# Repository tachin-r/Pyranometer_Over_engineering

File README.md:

# Pyranometer Over-engineering ☀️⚡

Modular High-Precision Pyranometer KiCad Hardware Project.

---

## 📑 Project Structure & Interactive Online Viewers

Explore the schematics and PCB layouts interactively directly in your browser powered by **KiCanvas** (no installation required):

| Board / Module | Description | Interactive Project (Schematic + PCB) | Schematic Only | PCB Only |
| :--- | :--- | :---: | :---: | :---: |
| **L1_Analog** | Analog Front-End & Sensor Interface | [🚀 Open L1 Board](https://kicanvas.org/?github=https://github.com/tachin-r/Pyranometer_Over_engineering/tree/main/L1_Analog) | [🔍 Schematic](https://kicanvas.org/?github=https://github.com/tachin-r/Pyranometer_Over_engineering/blob/main/L1_Analog/L1_Analog.kicad_sch) | [🔍 PCB](https://kicanvas.org/?github=https://github.com/tachin-r/Pyranometer_Over_engineering/blob/main/L1_Analog/L1_Analog.kicad_pcb) |
| **L2_MCU** | Microcontroller Processing Board | [🚀 Open L2 Board](https://kicanvas.org/?github=https://github.com/tachin-r/Pyranometer_Over_engineering/tree/main/L2_MCU) | [🔍 Schematic](https://kicanvas.org/?github=https://github.com/tachin-r/Pyranometer_Over_engineering/blob/main/L2_MCU/L2_MCU.kicad_sch) | [🔍 PCB](https://kicanvas.org/?github=https://github.com/tachin-r/Pyranometer_Over_engineering/blob/main/L2_MCU/L2_MCU.kicad_pcb) |
| **L3_Switching** | Power Management & Switching Regulators | [🚀 Open L3 Board](https://kicanvas.org/?github=https://github.com/tachin-r/Pyranometer_Over_engineering/tree/main/L3_Switching) | [🔍 Schematic](https://kicanvas.org/?github=https://github.com/tachin-r/Pyranometer_Over_engineering/blob/main/L3_Switching/L3_Switching.kicad_sch) | [🔍 PCB](https://kicanvas.org/?github=https://github.com/tachin-r/Pyranometer_Over_engineering/blob/main/L3_Switching/L3_Switching.kicad_pcb) |
| **LM2596 HW-411** | Reverse-Engineered Buck Converter Module | [🚀 Open LM2596](https://kicanvas.org/?github=https://github.com/tachin-r/Pyranometer_Over_engineering/tree/main/reverse_component/LM2596_HW411) | [🔍 Schematic](https://kicanvas.org/?github=https://github.com/tachin-r/Pyranometer_Over_engineering/blob/main/reverse_component/LM2596_HW411/LM2596_HW411.kicad_sch) | [🔍 PCB](https://kicanvas.org/?github=https://github.com/tachin-r/Pyranometer_Over_engineering/blob/main/reverse_component/LM2596_HW411/LM2596_HW411.kicad_pcb) |

---

## 🛠️ Boards Overview

### 1. `L1_Analog` (Sensor Front-End)
* Precision Analog Signal Conditioning stage designed for low-noise measurement of solar irradiance sensor signals (Pyranometer Thermopile / Photodiode).

### 2. `L2_MCU` (Processing & Control)
* Primary microcontroller board responsible for high-resolution ADC sampling, calibration algorithms, digital filtering, and telemetry communication.

### 3. `L3_Switching` (Power Distribution)
* Power supply unit (PSU) providing efficient switching regulation, clean power rail generation, and noise filtering for sensitive analog circuitry.

### 4. `reverse_component/LM2596_HW411`
* Reverse-engineered KiCad schematic and PCB layout of the common LM2596 HW-411 DC-DC step-down converter module, used for reference, testing, and validation.

---

## 🚀 Working with KiCad

This project is organized as a **modular multi-board system**:
* Each sub-directory contains its own standalone KiCad project file (`.kicad_pro`).
* To view or edit a board, open the corresponding `.kicad_pro` file inside its respective directory.

---

## 🔬 Capstone Documentation & Laboratory Calibration

* **[☀️ Solar Simulator Preparation & Contact Guide](file:///c:/Users/usEr/Documents/KiCad/10.0/projects/Pyranometer_Over_engineering/Report_doc/SOLAR_SIMULATOR_GUIDE.md)**: Contact templates, technical phone checklists, and procedures for using the **Solar Light XPS-300** at ATTAC / Nano Central Lab (Building 55, 3rd Floor).
* **[📷 Perfboard Photo & Figure Insertion Guide](file:///c:/Users/usEr/Documents/KiCad/10.0/projects/Pyranometer_Over_engineering/Report_doc/PHOTO_GUIDE_PERFBOARD.md)**: Complete image checklist and tips for inserting hardware photos into the report.
* **[📄 Capstone Progress Report V2 (.docx)](file:///c:/Users/usEr/Documents/KiCad/10.0/projects/Pyranometer_Over_engineering/Report_doc/69_IoT_Project1_Report_V2.docx)**: Official 5-chapter thesis report draft formatted to KMITL guidelines.

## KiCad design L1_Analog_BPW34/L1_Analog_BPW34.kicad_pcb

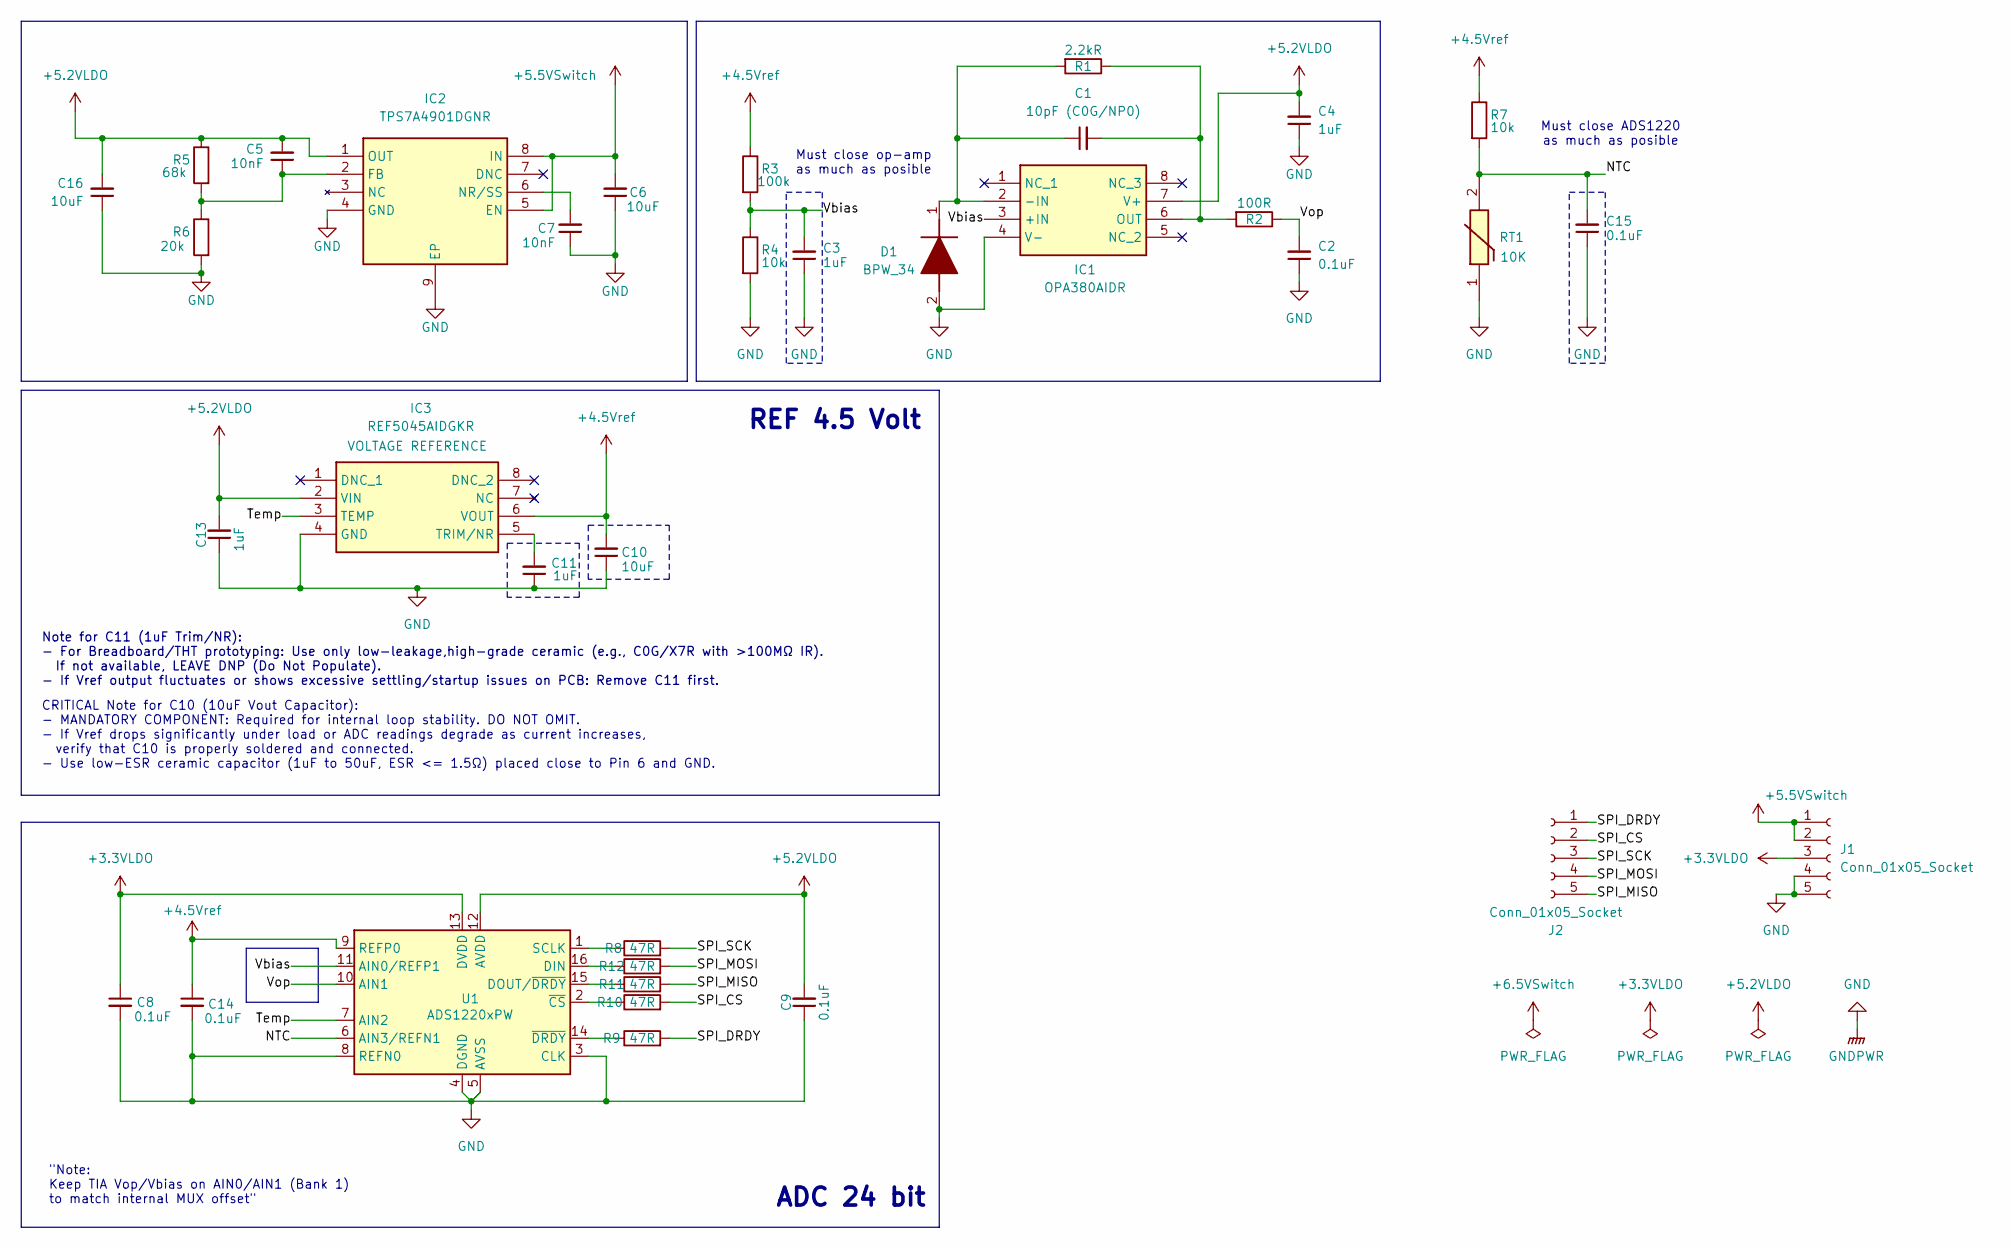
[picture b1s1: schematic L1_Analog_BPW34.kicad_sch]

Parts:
C1: 10pF (C0G/NP0); C_0805_2012Metric
C2, C8, C9, C14, C15: 0.1uF; C_0805_2012Metric
C3, C4, C11, C13: 1uF; C_0805_2012Metric
C5, C7: 10nF; C_0805_2012Metric
C6, C10, C16: 10uF; C_0805_2012Metric
D1: BPW_34; BPW34; Mouser Part Number 720-BPW34
IC1: OPA380AIDR; SOIC127P600X175-8N; Manufacturer_Part_Number OPA380AIDR; Mouser Part Number 595-OPA380AIDR
IC2: TPS7A4901DGNR; SOP65P490X110-9N; Manufacturer_Part_Number TPS7A4901DGNR; Mouser Part Number 595-TPS7A4901DGNR
IC3: REF5045AIDGKR; SOP65P490X110-8N; Mouser Part Number 595-REF5045AIDGKR
J1, J2: Conn_01x05_Socket; PinSocket_1x05_P2.54mm_Vertical
R1: 2.2kR; R_0805_2012Metric
R2: 100R; R_0805_2012Metric
R3: 100k; R_0805_2012Metric
R4, R7: 10k; R_0805_2012Metric
R5: 68k; R_0805_2012Metric
R6: 20k; R_0805_2012Metric
R8, R9, R10, R11, R12: 47R; R_0805_2012Metric
RT1: 10K; 103AT2; Manufacturer_Part_Number 103AT-2; Mouser Part Number 954-103AT-2
U1: ADS1220xPW; TSSOP-16_4.4x5mm_P0.65mm

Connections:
+3.3VLDO: C8.1, J1.3, U1.13 (DVDD)
+4.5Vref: C10.2, C14.1, IC3.6 (VOUT), R3.1, R7.1, U1.9 (REFP0)
+5.2VLDO: C4.2, C5.2, C9.2, C13.2, C16.2, IC1.7 (V+), IC2.1 (OUT), IC3.2 (VIN), R5.1, U1.12 (AVDD)
+5.5VSwitch: C6.2, IC2.5 (EN), IC2.8 (IN), J1.1, J1.2
/NTC: C15.2, R7.2, RT1.2, U1.6 (AIN3/REFN1)
/SPI_CS: J2.2, R10.2
/SPI_DRDY: J2.1, R9.2
/SPI_MISO: J2.5, R11.2
/SPI_MOSI: J2.4, R12.2
/SPI_SCK: J2.3, R8.2
/Temp: IC3.3 (TEMP), U1.7 (AIN2); also elsewhere on the board
/Vbias: C3.2, IC1.3 (+IN), R3.2, R4.1, U1.11 (AIN0/REFP1)
/Vop: C2.2, R2.1, U1.10 (AIN1)
GND: C2.1, C3.1, C4.1, C6.1, C7.1, C8.2, C9.1, C10.1, C11.1, C13.1, C14.2, C15.1, C16.1, D1.2 (A), IC1.4 (V-), IC2.4 (GND), IC2.9 (EP), IC3.4 (GND), J1.4, J1.5, R4.2, R6.2, RT1.1, U1.3 (CLK), U1.4 (DGND), U1.5 (AVSS), U1.8 (REFN0); also elsewhere on the board
unnamed: C1.1, D1.1 (K), IC1.2 (-IN), R1.2
unnamed: C1.2, IC1.6 (OUT), R1.1, R2.2
unnamed: C5.1, IC2.2 (FB), R5.2, R6.1
unnamed: C7.2, IC2.6 (NR/SS)
unnamed: C11.2, IC3.5 (TRIM/NR)
unnamed: R12.1, U1.16 (DIN)
unnamed: R11.1, U1.15 (DOUT/~DRDY)
unnamed: R8.1, U1.1 (SCLK)
unnamed: R10.1, U1.2 (~CS)
unnamed: R9.1, U1.14 (~DRDY)

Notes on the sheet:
Note for C11 (1uF Trim/NR): - For Breadboard/THT prototyping: Use only low-leakage,high-grade ceramic (e.g., C0G/X7R with >100MΩ IR). If not available, LEAVE DNP (Do Not Populate). - If Vref output fluctuates or shows excessive settling/startup issues on PCB: Remove C11 first.
"Note: Keep TIA Vop/Vbias on AIN0/AIN1 (Bank 1) to match internal MUX offset"
Must close ADS1220 as much as posible
Must close op-amp as much as posible
ADC 24 bit
CRITICAL Note for C10 (10uF Vout Capacitor): - MANDATORY COMPONENT: Required for internal loop stability. DO NOT OMIT. - If Vref drops significantly under load or ADC readings degrade as current increases, verify that C10 is properly soldered and connected. - Use low-ESR ceramic capacitor (1uF to 5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
REF 4.5 Volt

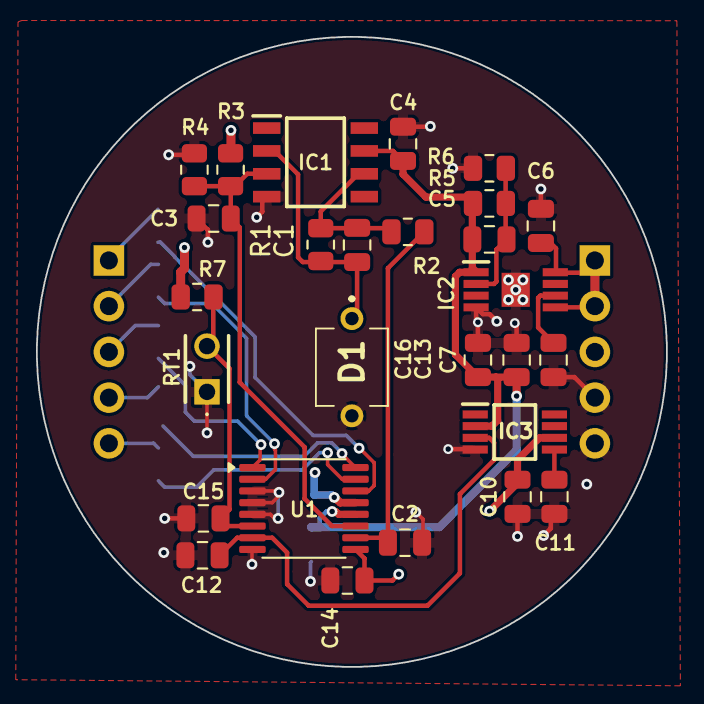
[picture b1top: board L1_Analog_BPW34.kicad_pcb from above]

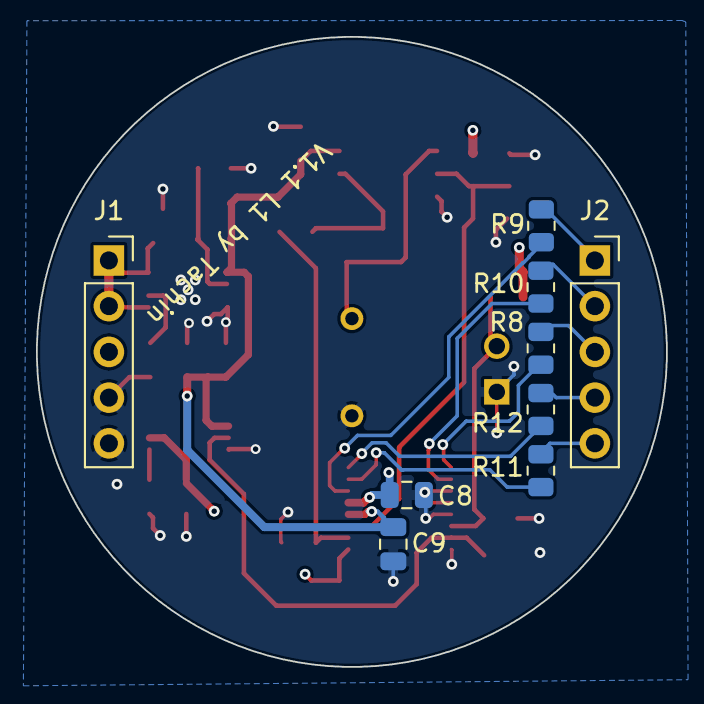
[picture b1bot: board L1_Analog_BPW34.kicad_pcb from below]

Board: 4 copper layers, 35.0 x 35.0 mm, 36 parts (9 on the bottom side), 24 nets.

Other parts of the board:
C12: 0.1uF; C_0805_2012Metric

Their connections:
/Temp: C12.2; also elsewhere on the board
GND: C12.1; also elsewhere on the board

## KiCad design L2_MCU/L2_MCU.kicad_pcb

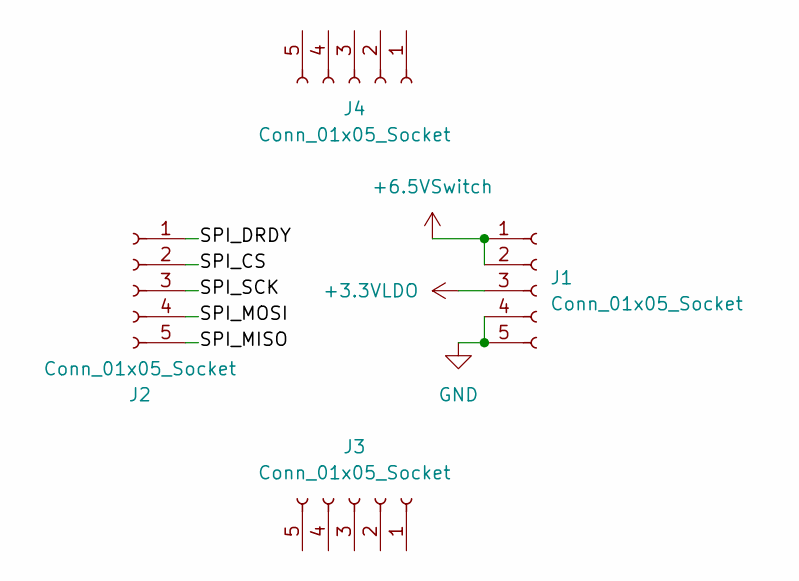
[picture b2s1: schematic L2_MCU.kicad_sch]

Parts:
J1, J2, J3, J4: Conn_01x05_Socket; PinHeader_1x05_P2.54mm_Vertical

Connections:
+3.3VLDO: J1.3
+6.5VSwitch: J1.1, J1.2
/SPI_CS: J2.2
/SPI_DRDY: J2.1
/SPI_MISO: J2.5
/SPI_MOSI: J2.4
/SPI_SCK: J2.3
GND: J1.4, J1.5

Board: 2 copper layers, 4 parts (2 on the bottom side), 2 nets, no tracks yet.

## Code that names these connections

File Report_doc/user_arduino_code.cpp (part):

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  // บน Perfboard: AIN0 = Vop, AIN1 = Vbias (สลับกับบน PCB)
  // -------------------------------------------------------------
  #define HW_TARGET_NAME "Perfboard Prototype"
  #define CH_VOP_IDX    0   // Vop อยู่ที่ AIN0
  #define CH_VBIAS_IDX  1   // Vbias อยู่ที่ AIN1
  #define CH_TEMP_IDX   2   // Temp (REF5045) อยู่ที่ AIN2
  #define CH_NTC_IDX    3   // NTC อยู่ที่ AIN3

  const char* CH_LABELS[4] = {
    "AIN0 (Vop - TIA Out)",
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  // บน PCB: AIN0 = Vbias, AIN1 = Vop (ตาม Schematic KiCad L1_Analog)
  // -------------------------------------------------------------
  #define HW_TARGET_NAME "Custom PCB (L1_Analog)"
  #define CH_VOP_IDX    1   // Vop อยู่ที่ AIN1
  #define CH_VBIAS_IDX  0   // Vbias อยู่ที่ AIN0
  #define CH_TEMP_IDX   2   // Temp (REF5045) อยู่ที่ AIN2
  #define CH_NTC_IDX    3   // NTC อยู่ที่ AIN3

  const char* CH_LABELS[4] = {
    "AIN0 (Vbias)",
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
